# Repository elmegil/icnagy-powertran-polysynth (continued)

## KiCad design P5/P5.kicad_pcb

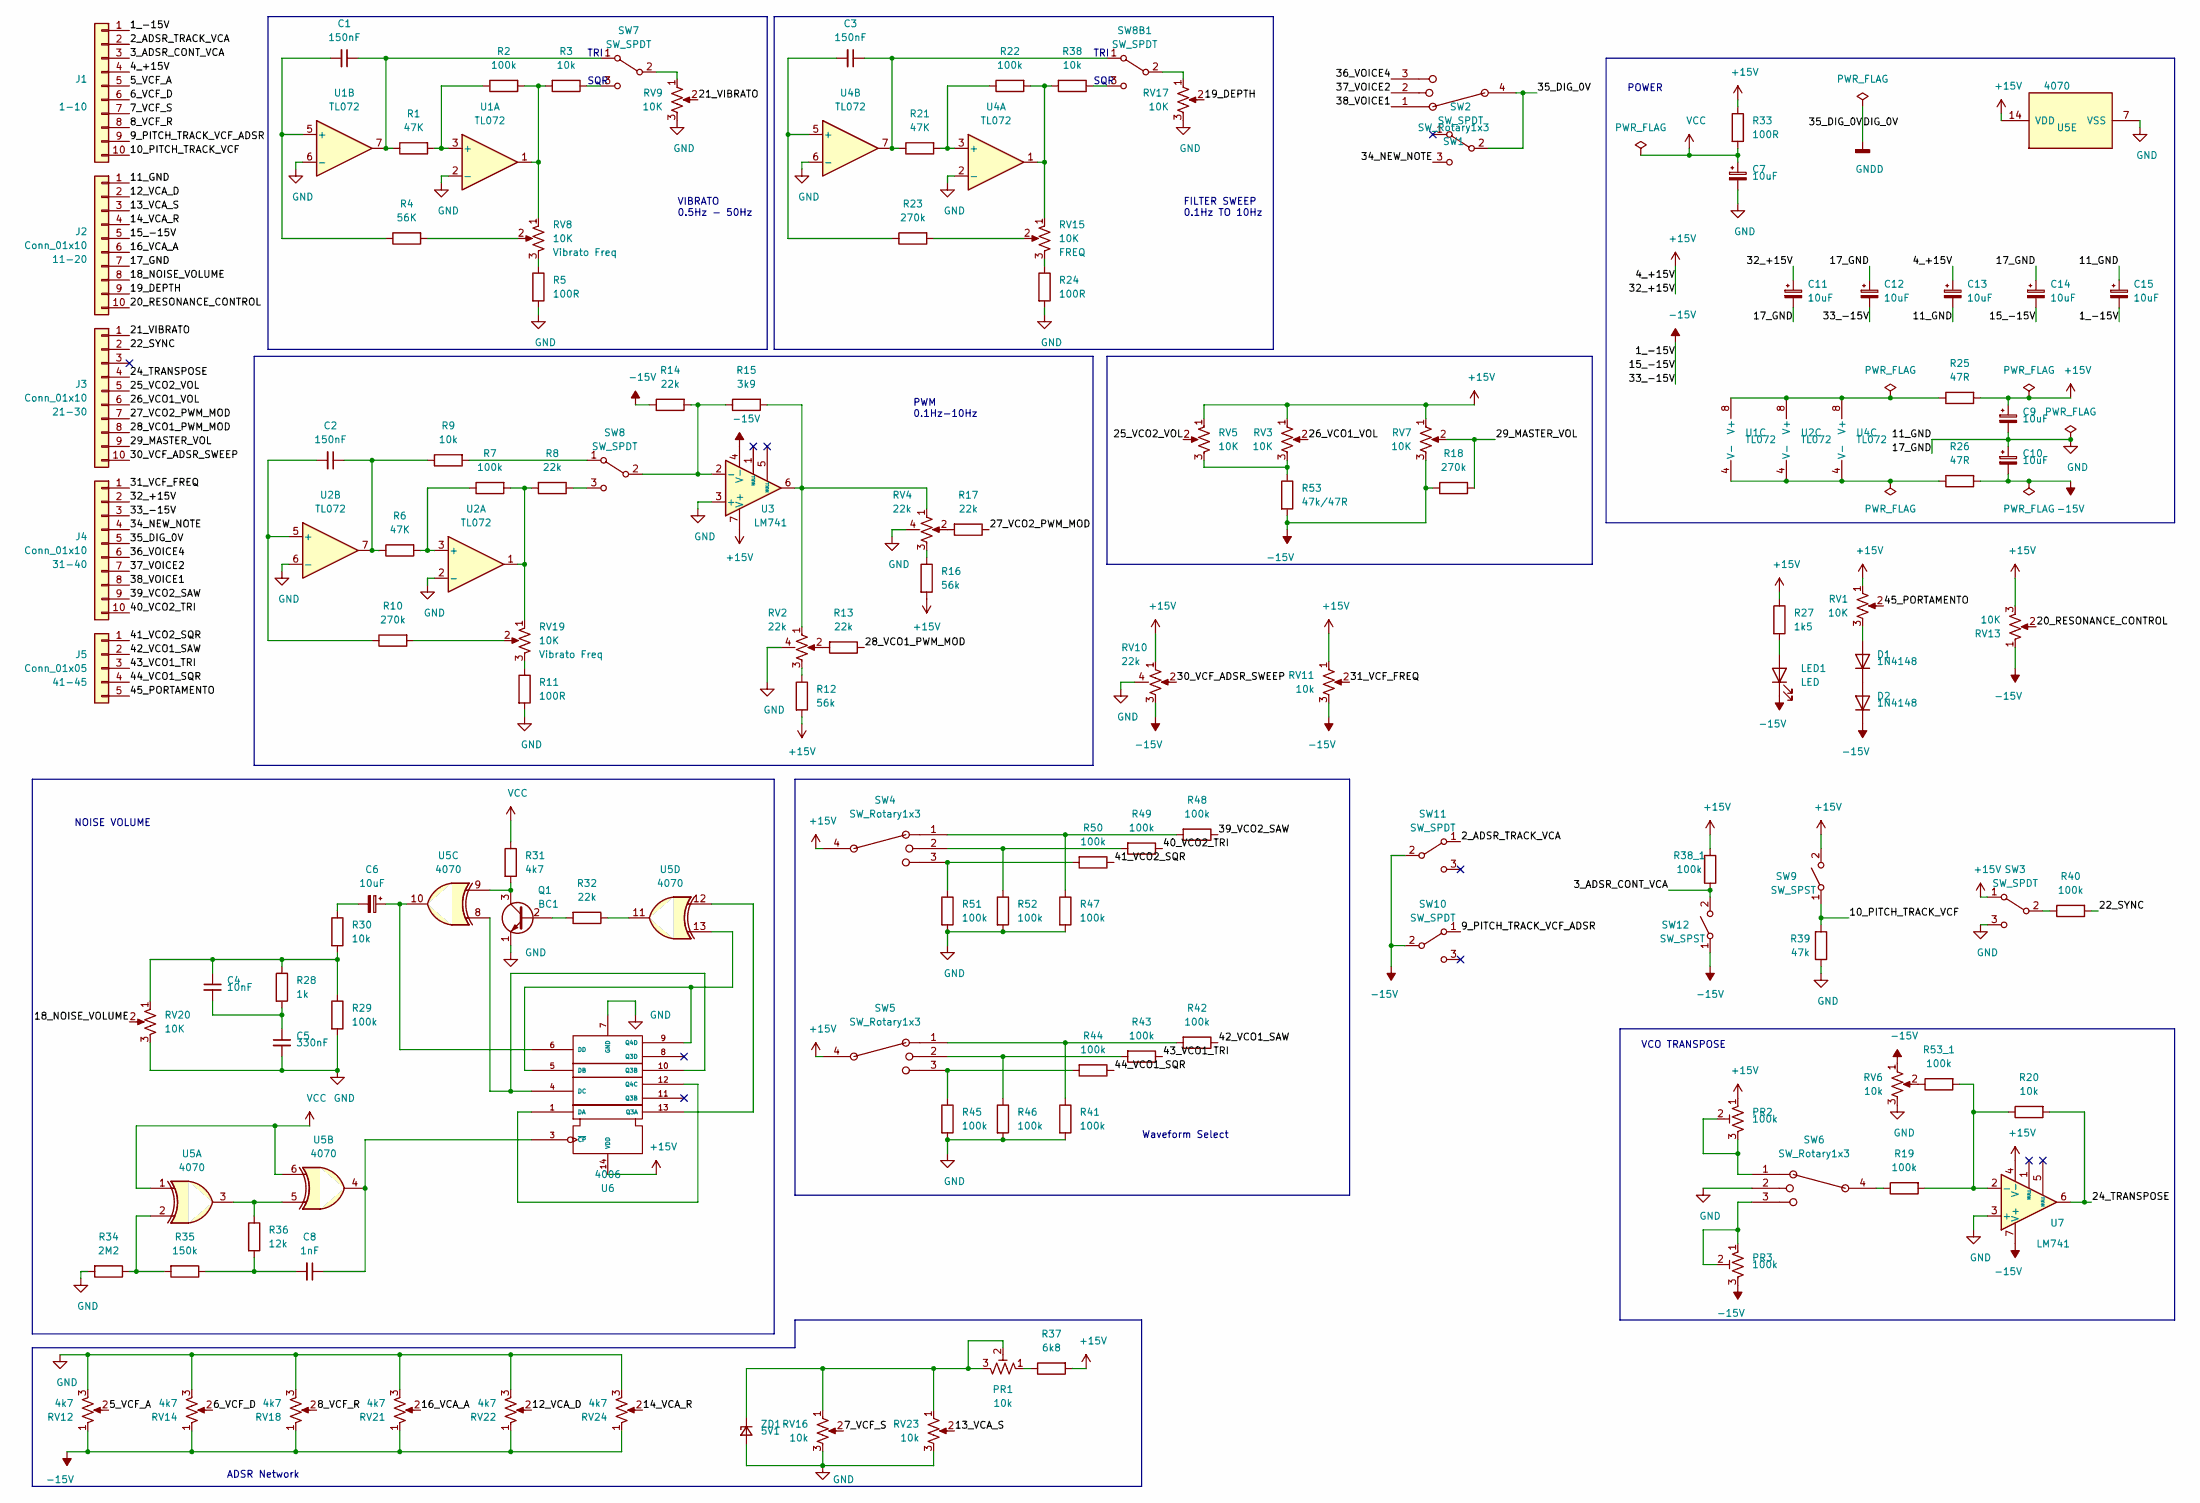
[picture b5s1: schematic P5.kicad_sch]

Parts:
C1, C2, C3: 150nF; C_Rect_L7.0mm_W3.5mm_P2.50mm_P5.00mm
C4: 10nF; C_Rect_L7.0mm_W3.5mm_P2.50mm_P5.00mm
C5: 330nF; C_Rect_L7.0mm_W3.5mm_P2.50mm_P5.00mm
C6, C7: 10uF; C_Rect_L7.0mm_W3.5mm_P2.50mm_P5.00mm
C8: 1nF; C_Rect_L7.0mm_W3.5mm_P2.50mm_P5.00mm
C9, C10, C11, C12, C13, C14, C15: 10uF; CP_Radial_D5.0mm_P2.50mm
D1, D2: 1N4148; D_DO-35_SOD27_P7.62mm_Horizontal
J1: 1-10; PinHeader_1x10_P2.54mm_Vertical
J2, J3, J4: Conn_01x10; PinHeader_1x10_P2.54mm_Vertical
J5: Conn_01x05; PinHeader_1x05_P2.54mm_Vertical
LED1: LED; LED_D3.0mm
PR1: 10k; Potentiometer_Bourns_3296W_Vertical
PR2, PR3: 100k; Potentiometer_Bourns_3296W_Vertical
Q1: BC1; TO-92L_Wide
R1, R6, R21: 47K; R_Axial_DIN0207_L6.3mm_D2.5mm_P10.16mm_Horizontal
R2, R7, R19, R22, R29, R38_1, R40, R41, R42, R43, R44, R45, R46, R47, R48, R49, R50, R51, R52, R53_1: 100k; R_Axial_DIN0207_L6.3mm_D2.5mm_P10.16mm_Horizontal
R3, R9, R20, R30, R38: 10k; R_Axial_DIN0207_L6.3mm_D2.5mm_P10.16mm_Horizontal
R4: 56K; R_Axial_DIN0207_L6.3mm_D2.5mm_P10.16mm_Horizontal
R5, R11, R24, R33: 100R; R_Axial_DIN0207_L6.3mm_D2.5mm_P10.16mm_Horizontal
R8, R13, R14, R17, R32: 22k; R_Axial_DIN0207_L6.3mm_D2.5mm_P10.16mm_Horizontal
R10, R18, R23: 270k; R_Axial_DIN0207_L6.3mm_D2.5mm_P10.16mm_Horizontal
R12, R16: 56k; R_Axial_DIN0207_L6.3mm_D2.5mm_P10.16mm_Horizontal
R15: 3k9; R_Axial_DIN0207_L6.3mm_D2.5mm_P10.16mm_Horizontal
R25, R26: 47R; R_Axial_DIN0207_L6.3mm_D2.5mm_P10.16mm_Horizontal
R27: 1k5; R_Axial_DIN0207_L6.3mm_D2.5mm_P10.16mm_Horizontal
R28: 1k; R_Axial_DIN0207_L6.3mm_D2.5mm_P10.16mm_Horizontal
R31: 4k7; R_Axial_DIN0207_L6.3mm_D2.5mm_P10.16mm_Horizontal
R34: 2M2; R_Axial_DIN0207_L6.3mm_D2.5mm_P10.16mm_Horizontal
R35: 150k; R_Axial_DIN0207_L6.3mm_D2.5mm_P10.16mm_Horizontal
R36: 12k; R_Axial_DIN0207_L6.3mm_D2.5mm_P10.16mm_Horizontal
R37: 6k8; R_Axial_DIN0207_L6.3mm_D2.5mm_P10.16mm_Horizontal
R39: 47k; R_Axial_DIN0207_L6.3mm_D2.5mm_P10.16mm_Horizontal
R53: 47k/47R; R_Axial_DIN0207_L6.3mm_D2.5mm_P10.16mm_Horizontal
RV1, RV3, RV5, RV7, RV8, RV9, RV13, RV15, RV17, RV19, RV20: 10K; Potentiometer_Omeg_PC16BU_Vertical
RV2, RV4, RV10: 22k; Potentiometer_Omeg_PC16BU_Vertical_Tapped
RV6, RV11, RV16, RV23: 10k; Potentiometer_Omeg_PC16BU_Vertical
RV12, RV14, RV18, RV21, RV22, RV24: 4k7; Potentiometer_Omeg_PC16BU_Vertical
SW1, SW4, SW5, SW6: SW_Rotary1x3; SR2612F-0304-18R0B-D8-N
SW2, SW3: SW_SPDT; SW_NKK_G1xJP
SW7, SW8, SW8B1, SW10, SW11: SW_SPDT; 11-SS-22-701C
SW9, SW12: SW_SPST; 11-SS-22-701C
U1, U2, U4: TL072; DIP-8_W7.62mm_LongPads
U3, U7: LM741; DIP-8_W7.62mm_LongPads
U5: 4070; DIP-14_W7.62mm_LongPads
U6: 4006; DIP-14_W7.62mm_LongPads
ZD1: 5V1; D_A-405_P10.16mm_Horizontal

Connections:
+15V: C9.1, C11.1, C13.1, J1.4, J4.2, PR2.1, R12.2, R16.2, R25.2, R27.1, R33.1, R37.2, R38_1.2, RV1.1, RV3.1, RV5.1, RV7.1, RV10.1, RV11.1, RV13.3, SW3.1 (A), SW4.4, SW5.4, SW9.2 (B), U3.7 (V+), U5.14 (VDD), U6.14 (VDD), U7.4 (V-)
-15V: C10.2, C12.2, C14.2, C15.2, D2.1 (K), J1.1, J2.5, J4.3, LED1.1 (K), PR3.3, R14.1, R18.1, R26.2, R53.2, RV6.1, RV7.3, RV10.3, RV11.3, RV12.1, RV13.1, RV14.1, RV18.1, RV21.1, RV22.1, RV24.1, SW10.2 (B), SW11.2 (B), SW12.1 (A), U3.4 (V-), U7.7 (V+)
/2_ADSR_TRACK_VCA: J1.2, SW11.1 (A)
/3_ADSR_CONT_VCA: J1.3, R38_1.1, SW12.2 (B)
/5_VCF_A: J1.5, RV12.2
/6_VCF_D: J1.6, RV14.2
/7_VCF_S: J1.7, RV16.2
/8_VCF_R: J1.8, RV18.2
/9_PITCH_TRACK_VCF_ADSR: J1.9, SW10.1 (A)
/10_PITCH_TRACK_VCF: J1.10, R39.2, SW9.1 (A)
/12_VCA_D: J2.2, RV22.2
/13_VCA_S: J2.3, RV23.2
/14_VCA_R: J2.4, RV24.2
/16_VCA_A: J2.6, RV21.2
/18_NOISE_VOLUME: J2.8, RV20.2
/19_DEPTH: J2.9, RV17.2
/20_RESONANCE_CONTROL: J2.10, RV13.2
/21_VIBRATO: J3.1, RV9.2
/22_SYNC: J3.2, R40.2
/24_TRANSPOSE: J3.4, R20.2, U7.6
/25_VCO2_VOL: J3.5, RV5.2
/26_VCO1_VOL: J3.6, RV3.2
/27_VCO2_PWM_MOD: J3.7, R17.1
/28_VCO1_PWM_MOD: J3.8, R13.1
/29_MASTER_VOL: J3.9, R18.2, RV7.2
/30_VCF_ADSR_SWEEP: J3.10, RV10.2
/31_VCF_FREQ: J4.1, RV11.2
/34_NEW_NOTE: J4.4, SW2.3 (C)
/36_VOICE4: J4.6, SW1.3
/37_VOICE2: J4.7, SW1.2
/38_VOICE1: J4.8, SW1.1
/39_VCO2_SAW: J4.9, R48.1
/40_VCO2_TRI: J4.10, R49.1
/41_VCO2_SQR: J5.1, R50.1
/42_VCO1_SAW: J5.2, R42.1
/43_VCO1_TRI: J5.3, R43.1
/44_VCO1_SQR: J5.4, R44.1
/45_PORTAMENTO: J5.5, RV1.2
GND: C5.2, C7.2, C9.2, C10.1, C11.2, C12.1, C13.2, C14.1, C15.1, J2.1, J2.7, Q1.1 (E), R5.2, R11.2, R24.2, R29.2, R34.2, R39.1, R41.2, R45.2, R46.2, R47.2, R51.2, R52.2, RV2.4, RV4.4, RV6.3, RV9.3, RV10.4, RV12.3, RV14.3, RV16.3, RV17.3, RV18.3, RV20.3, RV21.3, RV22.3, RV23.3, RV24.3, SW3.3 (C), SW6.2, U1.2 (-), U1.6 (-), U2.2 (-), U2.6 (-), U3.3 (+), U4.2 (-), U4.6 (-), U5.7 (VSS), U6.7 (GND), U7.3 (+), ZD1.2 (A)
GNDD: J4.5, SW1.4, SW2.2 (B)
unnamed: C1.1, R1.1, SW7.1 (A), U1.7
unnamed: C1.2, R4.1, U1.5 (+)
unnamed: C2.1, R6.1, R9.1, U2.7
unnamed: C2.2, R10.1, U2.5 (+)
unnamed: C3.1, R21.1, SW8B1.1 (A), U4.7
unnamed: C3.2, R23.1, U4.5 (+)
unnamed: C4.1, R28.1, R29.1, R30.2, RV20.1
unnamed: C4.2, C5.1, R28.2
unnamed: C6.1, U5.10, U6.6 (DD)
unnamed: C6.2, R30.1
unnamed: C8.1, U5.4, U6.3 (~CP)
unnamed: C8.2, R35.1, R36.2
unnamed: D1.1 (K), D2.2 (A)
unnamed: D1.2 (A), RV1.3
unnamed: LED1.2 (A), R27.2
unnamed: PR1.1, R37.1
unnamed: PR1.2, PR1.3, RV16.1, RV23.1, ZD1.1 (K)
unnamed: PR2.2, PR2.3, SW6.1
unnamed: PR3.1, PR3.2, SW6.3
unnamed: Q1.2 (B), R32.2
unnamed: Q1.3 (C), R31.2, U5.9
unnamed: R1.2, R2.1, U1.3 (+)
unnamed: R2.2, R3.2, RV8.1, U1.1
unnamed: R3.1, SW7.3 (C)
unnamed: R4.2, RV8.2
unnamed: R5.1, RV8.3
unnamed: R6.2, R7.1, U2.3 (+)
unnamed: R7.2, R8.2, RV19.1, U2.1
unnamed: R8.1, SW8.3 (C)
unnamed: R9.2, SW8.1 (A)
unnamed: R10.2, RV19.2
unnamed: R11.1, RV19.3
unnamed: R12.1, RV2.3
unnamed: R13.2, RV2.2
unnamed: R14.2, R15.1, SW8.2 (B), U3.2 (-)
unnamed: R15.2, RV2.1, RV4.1, U3.6
unnamed: R16.1, RV4.3
unnamed: R17.2, RV4.2
unnamed: R19.1, SW6.4
unnamed: R19.2, R20.1, R53_1.2, U7.2 (-)
unnamed: R21.2, R22.1, U4.3 (+)
unnamed: R22.2, R38.2, RV15.1, U4.1
unnamed: R23.2, RV15.2
unnamed: R24.1, RV15.3
unnamed: R25.1, U1.8 (V+), U2.8 (V+), U4.8 (V+)
unnamed: R26.1, U1.4 (V-), U2.4 (V-), U4.4 (V-)
unnamed: R32.1, U5.11
unnamed: R34.1, R35.2, U5.2
unnamed: R36.1, U5.3, U5.5
unnamed: R38.1, SW8B1.3 (C)
unnamed: R40.1, SW3.2 (B)
unnamed: R41.1, R42.2, SW5.1
unnamed: R43.2, R46.1, SW5.2
unnamed: R44.2, R45.1, SW5.3
unnamed: R47.1, R48.2, SW4.1
unnamed: R49.2, R52.1, SW4.2
unnamed: R50.2, R51.1, SW4.3
unnamed: R53.1, RV3.3, RV5.3
unnamed: R53_1.1, RV6.2
unnamed: RV9.1, SW7.2 (B)
unnamed: RV17.1, SW8B1.2 (B)
unnamed: U5.8, U6.4 (DC), U6.10 (Q3B)
unnamed: U5.12, U6.13 (Q3A)
unnamed: U5.13, U6.5 (DB), U6.9 (Q4D)
unnamed: U6.1 (DA), U6.12 (Q4C)
VCC: C7.1, R31.1, R33.2, U5.1, U5.6

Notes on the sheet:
SQR
TRI
POWER
PWM 0.1Hz-10Hz
Waveform Select
VIBRATO 0.5Hz - 50Hz
ADSR Network
VCO TRANSPOSE
NOISE VOLUME
FILTER SWEEP 0.1Hz TO 10Hz

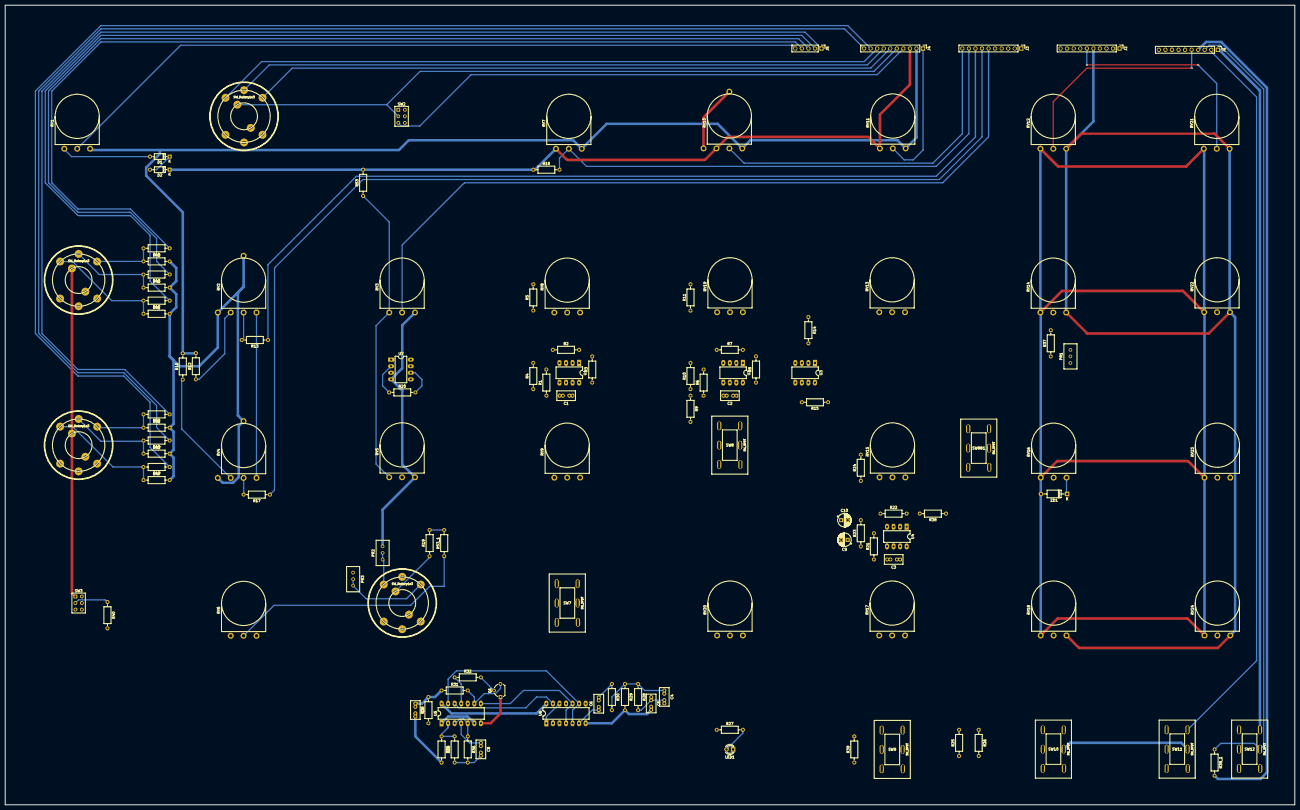
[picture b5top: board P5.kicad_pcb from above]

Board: 2 copper layers, 500.0 x 310.0 mm, 122 parts (0 on the bottom side), 106 nets.

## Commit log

2020-06-18 Add PS6 board
2020-06-18 Finish PS6
2020-06-18 Add PS4 schematics
2020-06-18 Update PS3 & PS5
2020-07-01 PS4 pcb layout
2020-07-01 Add PS4 documents
2020-07-02 Update PS4 board/schematic
2020-07-18 Place components on P5, add front panel
2020-07-18 Fix P5 VCA/VCF A/D/R pots orientation
2020-07-19 P5 layout in progress
2022-04-09 P3 layout in progress
2022-04-10 P3 layout in progress 2
2022-04-15 P4 layout in progress
2023-01-22 Upgrate P3 to Kicad 6 and update pcb layout
2023-01-22 Upgrate P4 to Kicad 6 and update pcb layout
2023-02-16 Updatee P5 to Kicad 6 and update pcb layout
2023-03-16 Update P1-2 to KiCad 7
2023-03-16 Finish P1-2
2023-03-16 Update P3 to KiCad 7
2023-03-16 Update P5 to KiCad 7
2023-03-16 Update P4 to KiCad 7
2023-08-18 Update P1-2 and ignore backups
2023-08-18 Update P6 to KiCad 7
